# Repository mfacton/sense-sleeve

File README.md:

# sense-sleeve
Pressure Sensing Sleeve

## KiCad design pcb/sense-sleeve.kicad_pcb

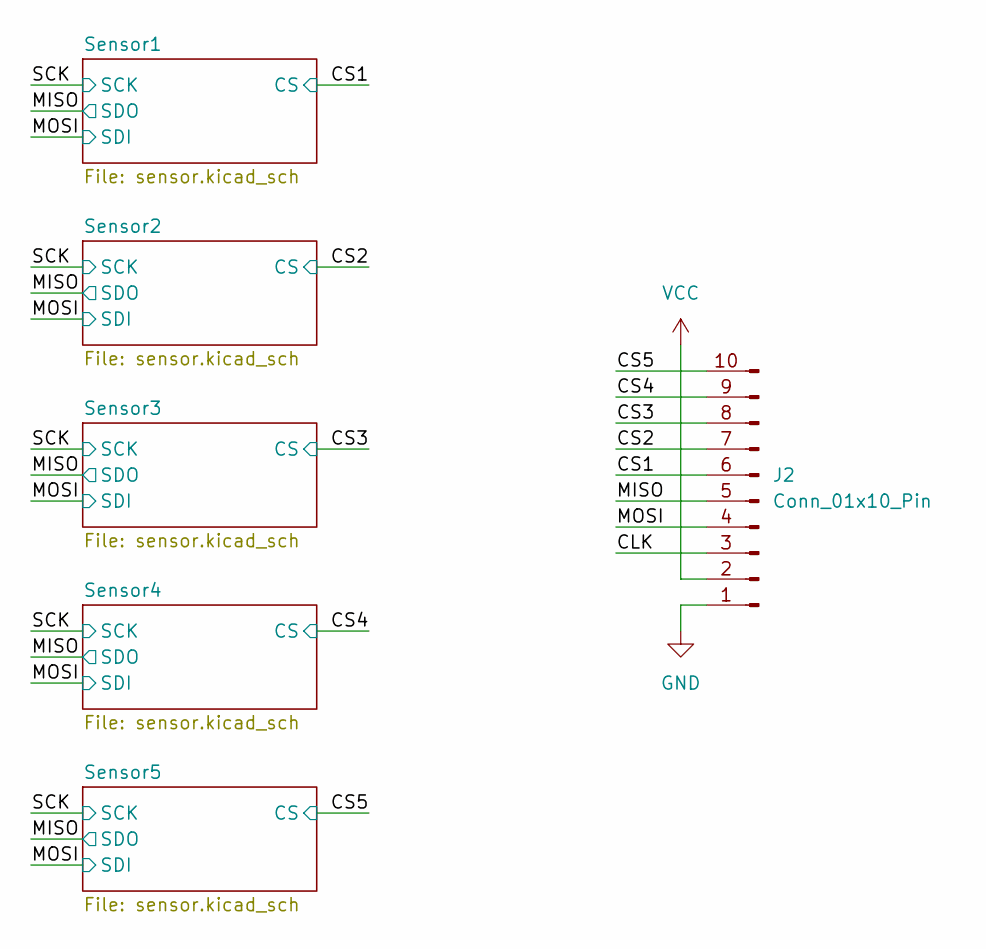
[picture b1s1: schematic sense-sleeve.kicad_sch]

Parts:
J2: Conn_01x10_Pin; FPC_10P_P0.5mm

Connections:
/CLK: J2.3
/CS1: J2.6; also elsewhere on the board
/CS2: J2.7; also elsewhere on the board
/CS3: J2.8; also elsewhere on the board
/CS4: J2.9; also elsewhere on the board
/CS5: J2.10; also elsewhere on the board
/MISO: J2.5; also elsewhere on the board
/MOSI: J2.4; also elsewhere on the board
GND: J2.1; also elsewhere on the board
VCC: J2.2

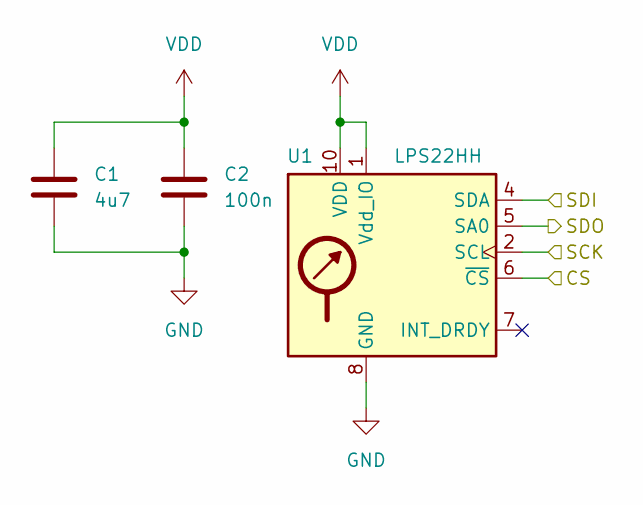
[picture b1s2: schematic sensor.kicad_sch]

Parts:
C1: 4u7; C_0402_1005Metric; LCSC C23733
C2: 100n; C_0402_1005Metric; LCSC C1525
U1: LPS22HH; ST_HLGA-10_2x2mm_P0.5mm_LayoutBorder3x2y; LCSC C2827824

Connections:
/CS1: U1.6 (~CS); also elsewhere on the board
/MISO: U1.5 (SA0); also elsewhere on the board
/MOSI: U1.4 (SDA); also elsewhere on the board
/SCK: U1.2 (SCL); also elsewhere on the board
GND: C1.2, C2.2, U1.3 (GND), U1.8 (GND), U1.9 (GND); also elsewhere on the board
VDD: C1.1, C2.1, U1.1 (Vdd_IO), U1.10 (VDD); also elsewhere on the board

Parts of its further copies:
C3, C5, C7, C9: 4u7; C_0402_1005Metric; LCSC C23733
C4, C6, C8, C10: 100n; C_0402_1005Metric; LCSC C1525
U2, U3, U4, U5: LPS22HH; ST_HLGA-10_2x2mm_P0.5mm_LayoutBorder3x2y; LCSC C2827824

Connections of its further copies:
/CS2: U2.6 (~CS); also elsewhere on the board
/CS3: U3.6 (~CS); also elsewhere on the board
/CS4: U4.6 (~CS); also elsewhere on the board
/CS5: U5.6 (~CS); also elsewhere on the board
/MISO: U2.5 (SA0), U3.5 (SA0), U4.5 (SA0), U5.5 (SA0); also elsewhere on the board
/MOSI: U2.4 (SDA), U3.4 (SDA), U4.4 (SDA), U5.4 (SDA); also elsewhere on the board
/SCK: U2.2 (SCL), U3.2 (SCL), U4.2 (SCL), U5.2 (SCL); also elsewhere on the board
GND: C3.2, C4.2, C5.2, C6.2, C7.2, C8.2, C9.2, C10.2, U2.3 (GND), U2.8 (GND), U2.9 (GND), U3.3 (GND), U3.8 (GND), U3.9 (GND), U4.3 (GND), U4.8 (GND), U4.9 (GND), U5.3 (GND), U5.8 (GND), U5.9 (GND); also elsewhere on the board
VDD: C3.1, C4.1, C5.1, C6.1, C7.1, C8.1, C9.1, C10.1, U2.1 (Vdd_IO), U2.10 (VDD), U3.1 (Vdd_IO), U3.10 (VDD), U4.1 (Vdd_IO), U4.10 (VDD), U5.1 (Vdd_IO), U5.10 (VDD); also elsewhere on the board

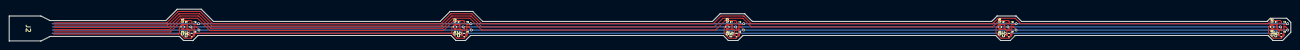
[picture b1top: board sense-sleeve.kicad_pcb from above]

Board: 2 copper layers, 282.3 x 7.0 mm, 16 parts (0 on the bottom side), 10 nets.

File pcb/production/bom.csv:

Designator,Footprint,Quantity,Value,LCSC Part #
"C1, C3, C5, C7, C9",0402,5,4u7,C23733
"C10, C2, C4, C6, C8",0402,5,100n,C1525
"U1, U2, U3, U4, U5",ST_HLGA-10_2x2mm_P0.5mm_LayoutBorder3x2y,5,LPS22HH,C2827824

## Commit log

2024-09-04 Create flexible sleeve pcb
